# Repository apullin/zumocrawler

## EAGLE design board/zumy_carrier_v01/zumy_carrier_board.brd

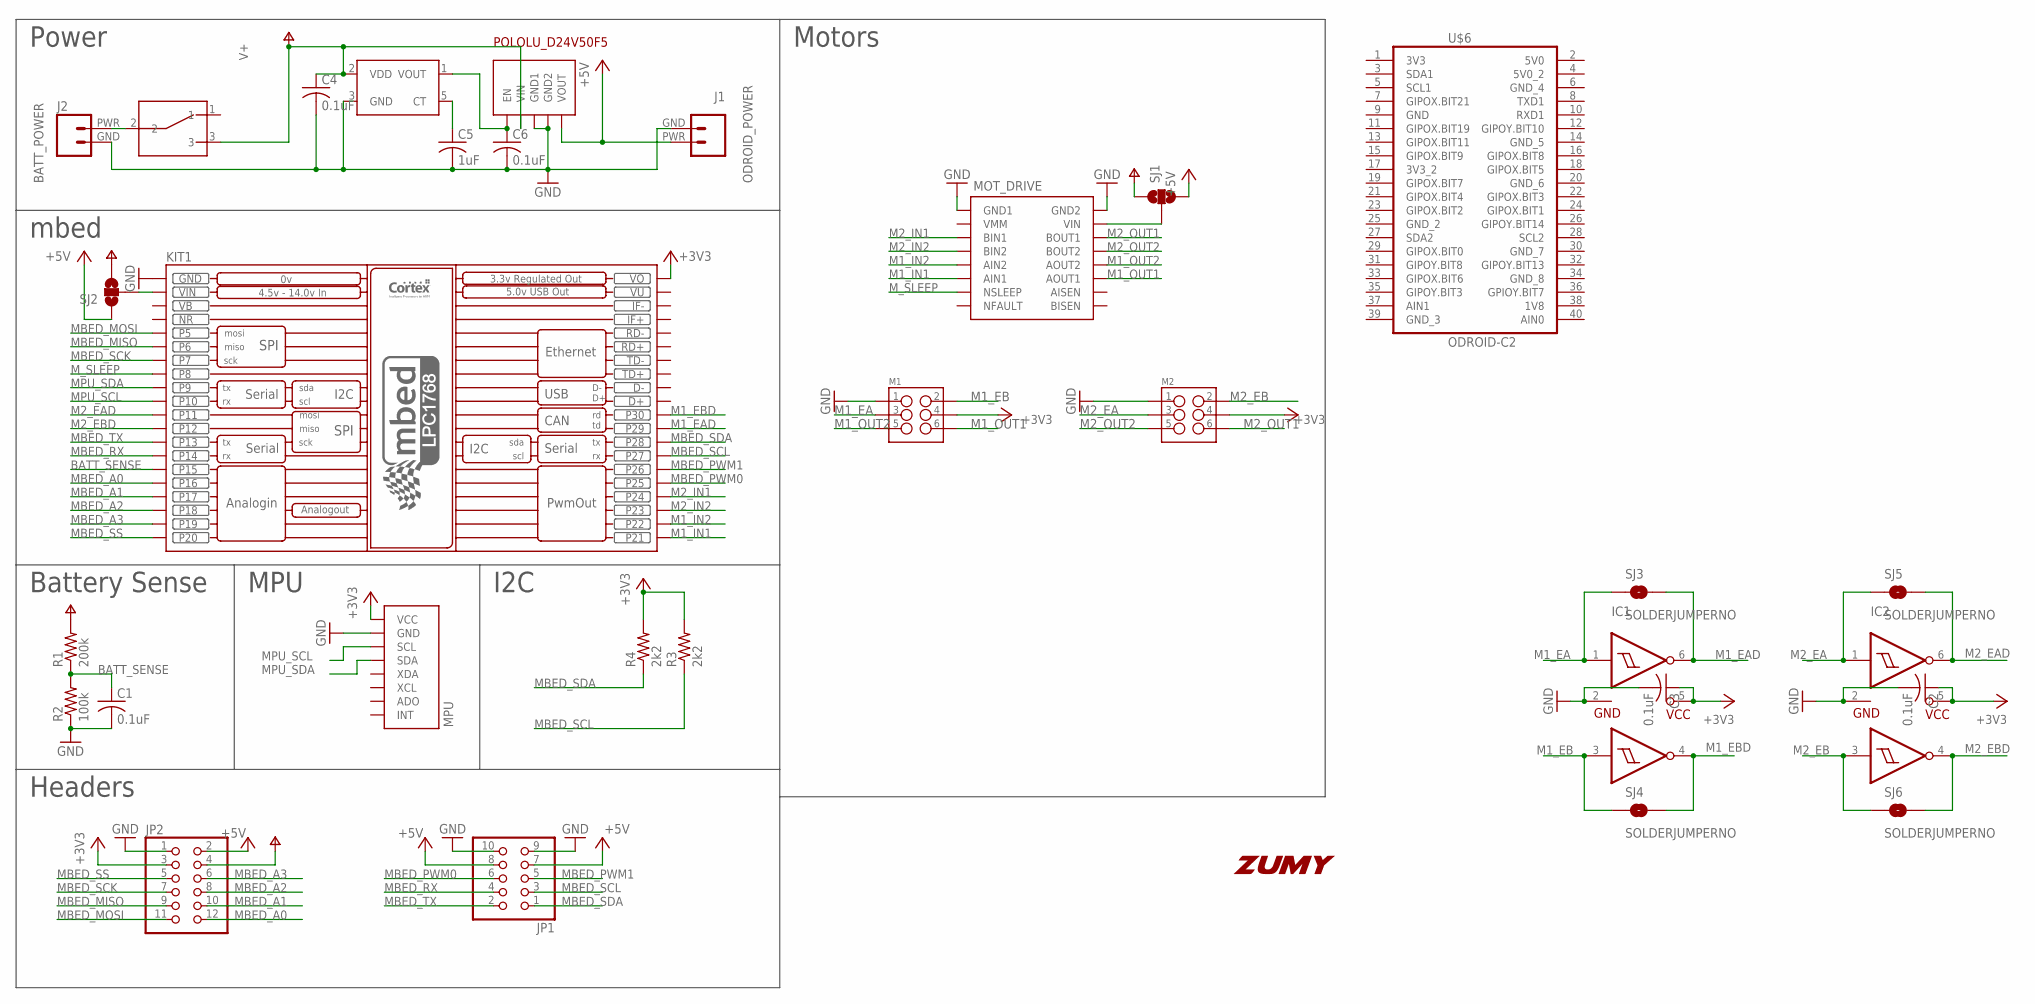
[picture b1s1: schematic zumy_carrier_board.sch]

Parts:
C1, C2, C3, C4, C6: 0.1uF; C1206
C5: 1uF; C1206
IC1, IC2: SN74AUP2G17; SC-70-6
J1: ODROID_POWER; ODOIRD_PWR
J2: BATT_POWER
JP1: PINHD-2X5; 2X05
JP2: PINHD-2X6; 2X06
KIT1: MBED_NXP_LPC1768; MBED-KIT
M1, M2: M03X2SHROUD; 2X3-SHROUDED
MOT_DRIVE: POLOLU_DRV8833_MODULE
MPU: ITG/MPU_MODULE
R1: 200k; R1206
R2: 100k; R1206
R3, R4: 2k2; R1206
SJ1, SJ2: SOLDERJUMPER_2WAYT; SJ_2
SJ3, SJ4, SJ5, SJ6: SOLDERJUMPERNO; SJ_2S-NO
SW1: 500SSP1S1M6QEA; 500SSP1S1M6QEA_SWITCH
U$2: BD5260G; SOT23-5
U$3: ZUMY_LOGO; ZUMY_LOGO_SILK
U$5: POLOLU_D24V50F5
U$6: ODROID-C2; ODROID-C2-BOARD

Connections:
+3V3: C2.1, C3.1, IC1.5 (VCC), IC2.5 (VCC), JP2.3, KIT1.VOUT (VO), M1.4, M2.4, MPU.VCC, R3.2, R4.2
+5V: J1.PWR, JP1.7, JP1.8, JP2.2, SJ1.3, SJ2.1, U$5.VOUT
BATT_SENSE: C1.1, KIT1.P$15 (P15), R1.1, R2.2
GND: C1.2, C2.2, C3.2, C4.2, C5.2, C6.2, IC1.2 (GND), IC2.2 (GND), J1.GND, J2.GND, JP1.9, JP1.10, JP2.1, KIT1.GND, M1.1, M2.1, MOT_DRIVE.GND1, MOT_DRIVE.GND2, MPU.GND, R2.1, U$2.3 (GND), U$5.GND1, U$5.GND2
M1_EA: IC1.1 (1A), M1.3, SJ3.1
M1_EAD: IC1.6 (1Y), KIT1.P$29 (P29), SJ3.2
M1_EB: IC1.3 (2A), M1.2, SJ4.1
M1_EBD: IC1.4 (2Y), KIT1.P$30 (P30), SJ4.2
M1_IN1: KIT1.P$21 (P21), MOT_DRIVE.AIN1
M1_IN2: KIT1.P$22 (P22), MOT_DRIVE.AIN2
M1_OUT1: M1.6, MOT_DRIVE.AOUT1
M1_OUT2: M1.5, MOT_DRIVE.AOUT2
M2_EA: IC2.1 (1A), M2.3, SJ5.1
M2_EAD: IC2.6 (1Y), KIT1.P$11 (P11), SJ5.2
M2_EB: IC2.3 (2A), M2.2, SJ6.1
M2_EBD: IC2.4 (2Y), KIT1.P$12 (P12), SJ6.2
M2_IN1: KIT1.P$24 (P24), MOT_DRIVE.BIN1
M2_IN2: KIT1.P$23 (P23), MOT_DRIVE.BIN2
M2_OUT1: M2.6, MOT_DRIVE.BOUT1
M2_OUT2: M2.5, MOT_DRIVE.BOUT2
MBED_A0: JP2.12, KIT1.P$16 (P16)
MBED_A1: JP2.10, KIT1.P$17 (P17)
MBED_A2: JP2.8, KIT1.P$18 (P18)
MBED_A3: JP2.6, KIT1.P$19 (P19)
MBED_MISO: JP2.9, KIT1.P$6 (P6)
MBED_MOSI: JP2.11, KIT1.P$5 (P5)
MBED_PWM0: JP1.6, KIT1.P$25 (P25)
MBED_PWM1: JP1.5, KIT1.P$26 (P26)
MBED_RX: JP1.4, KIT1.P$14 (P14)
MBED_SCK: JP2.7, KIT1.P$7 (P7)
MBED_SCL: JP1.3, KIT1.P$27 (P27), R3.1
MBED_SDA: JP1.1, KIT1.P$28 (P28), R4.1
MBED_SS: JP2.5, KIT1.P$20 (P20)
MBED_TX: JP1.2, KIT1.P$13 (P13)
MPU_SCL: KIT1.P$10 (P10), MPU.SCL
MPU_SDA: KIT1.P$9 (P9), MPU.SDA
M_SLEEP: KIT1.P$8 (P8), MOT_DRIVE.NSLEEP
unnamed: KIT1.VIN, SJ2.2
unnamed: J2.PWR, SW1.2
unnamed: MOT_DRIVE.VIN, SJ1.2
unnamed: C6.1, U$2.1 (VOUT), U$5.EN
unnamed: C5.1, U$2.5 (CT)
NR: KIT1.NR
V+: C4.1, JP2.4, R1.2, SJ1.1, SJ2.3, SW1.3, U$2.2 (VDD), U$5.VIN
VB: KIT1.VB
VU: KIT1.VU

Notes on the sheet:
Motors
Power
mbed
MPU
I2C
Headers
Battery Sense

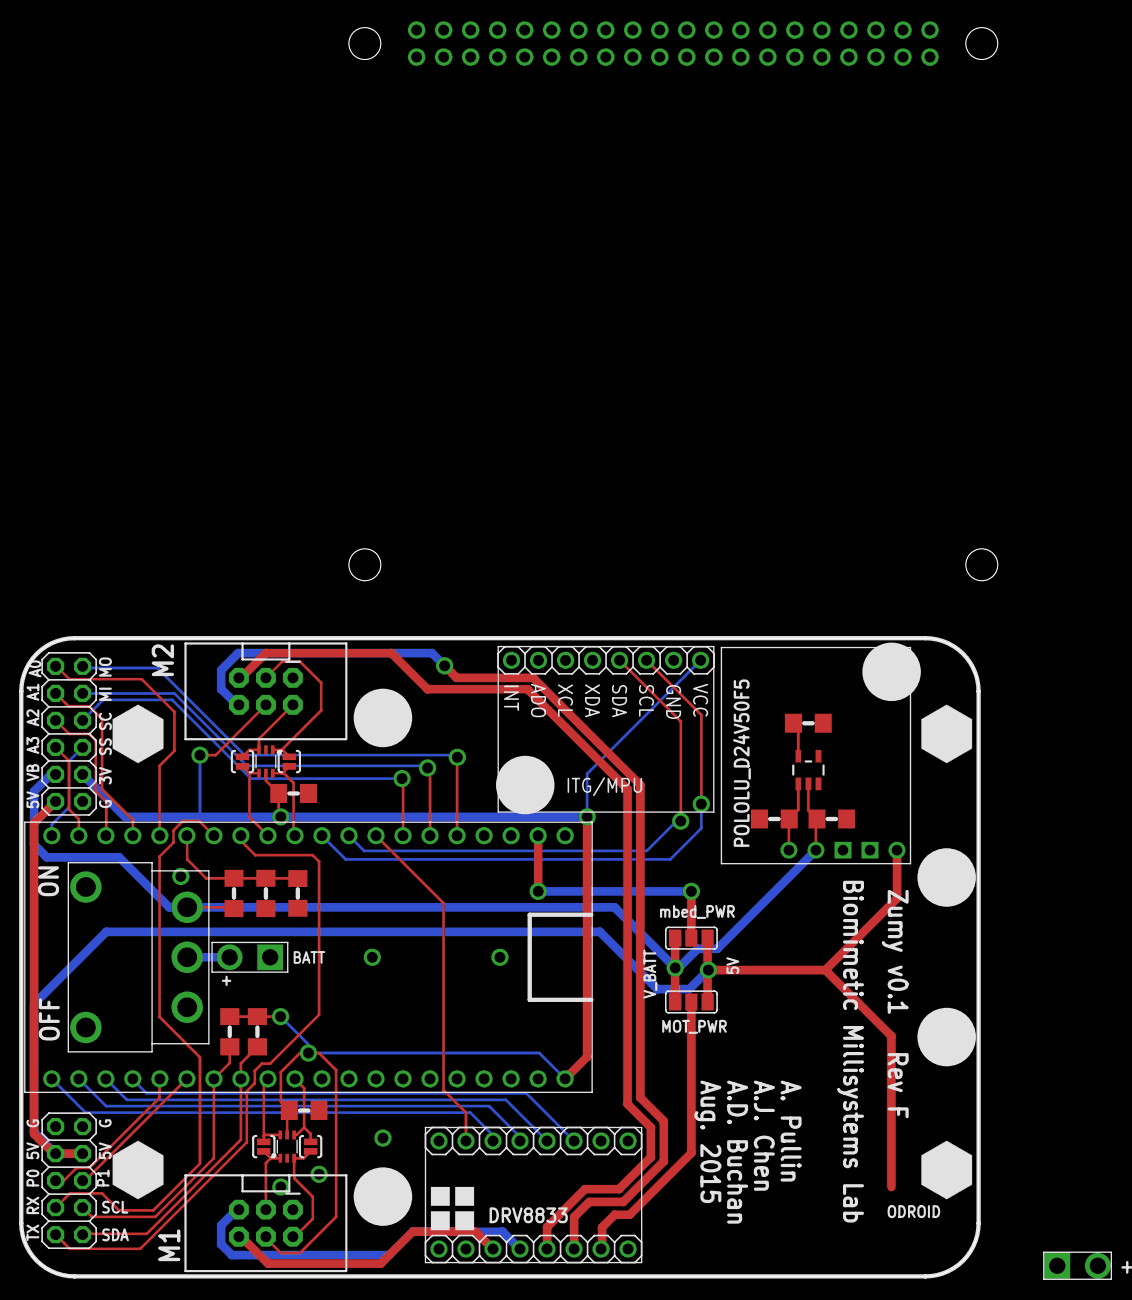
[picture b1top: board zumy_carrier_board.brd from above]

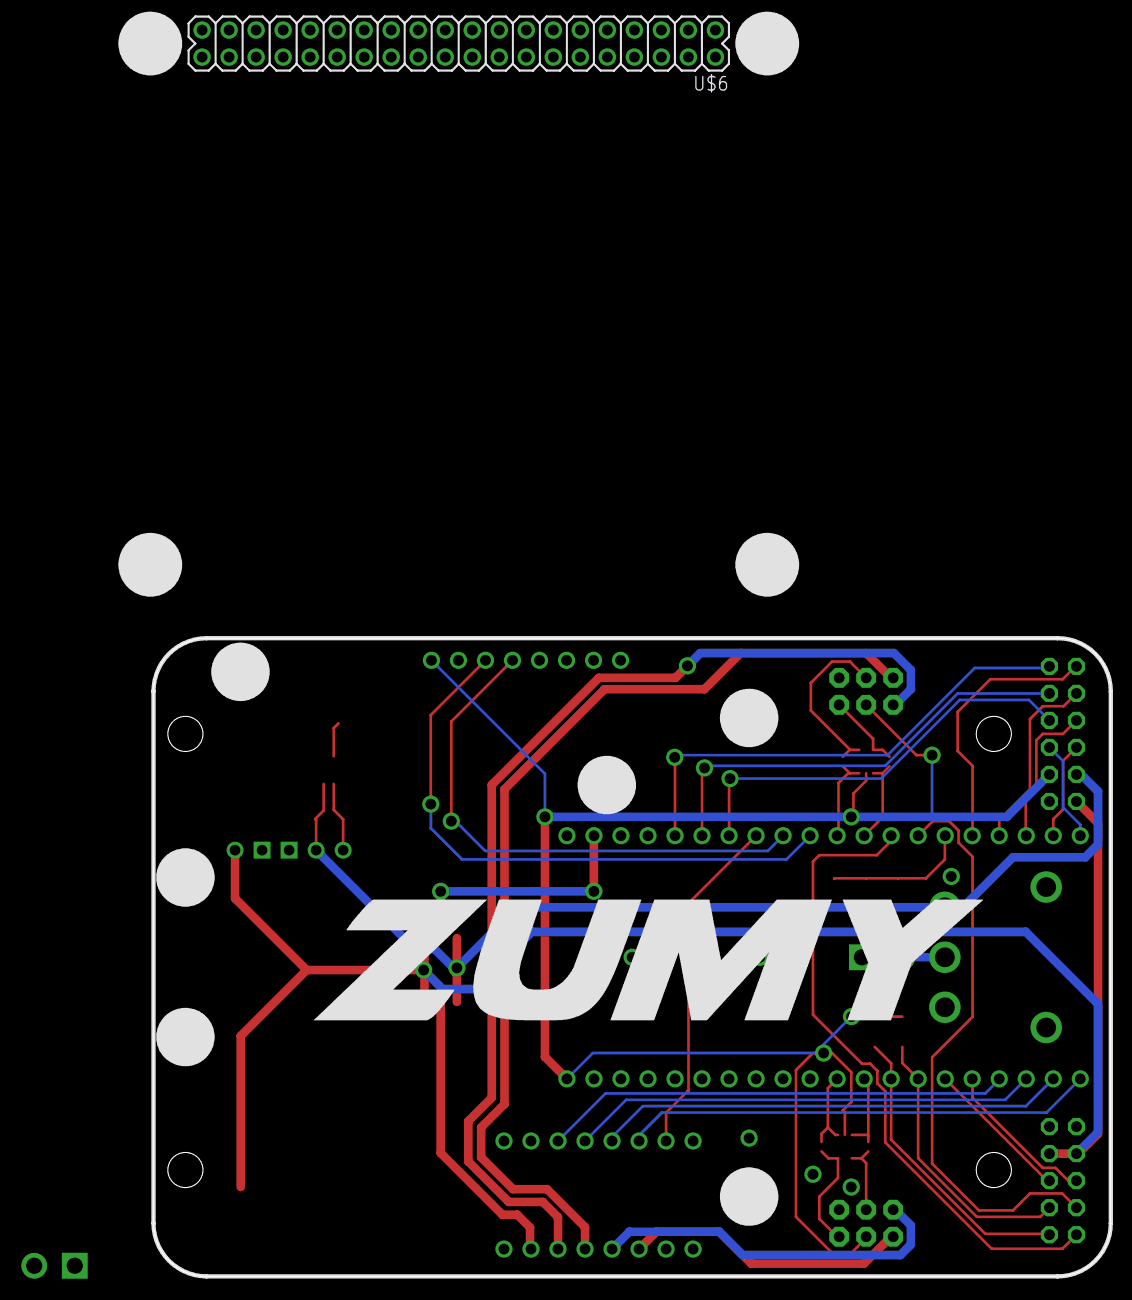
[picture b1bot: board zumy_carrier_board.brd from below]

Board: 2 copper layers, 90.0 x 60.0 mm, 34 parts (2 on the bottom side), 43 nets.

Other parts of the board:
U$1: CHASSIS_STANDOFF
U$4: ODROID_U3_MOUNTING

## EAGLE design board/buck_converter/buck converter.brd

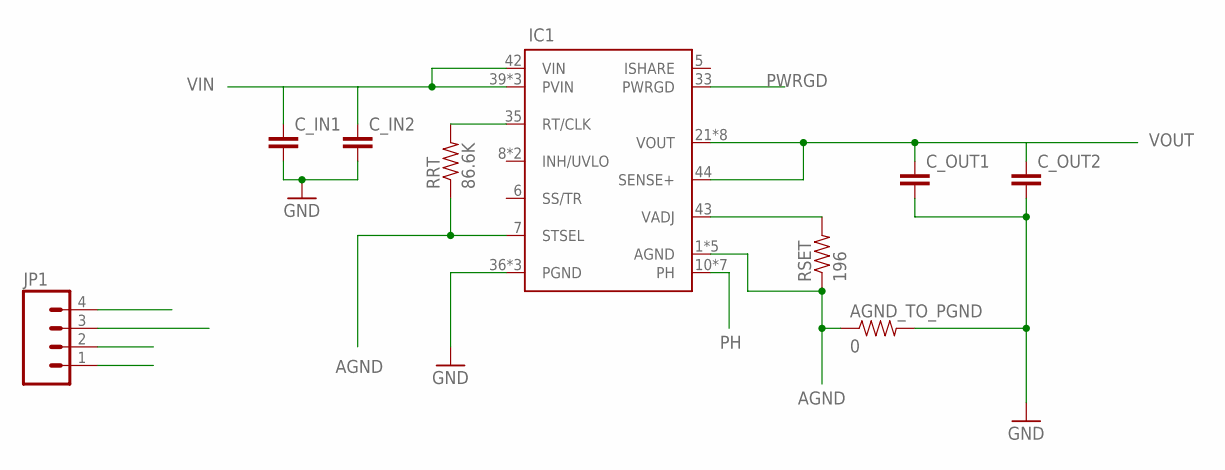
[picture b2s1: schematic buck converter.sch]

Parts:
AGND_TO_PGND: 0; 0402-RES
C_IN1, C_IN2: CAP1210; 1210
C_OUT1, C_OUT2: CAP1210; 1210
IC1: TPS84621
JP1: M04PTH; 1X04
RRT: 86.6K; 0402-RES
RSET: 196; 0402-RES

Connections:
AGND: AGND_TO_PGND.1, IC1.1 (AGND), IC1.2 (AGND), IC1.7 (STSEL), IC1.34 (AGND), IC1.45 (AGND), IC1.45B (AGND), RRT.1, RSET.1
GND: AGND_TO_PGND.2, C_IN1.2, C_IN2.2, C_OUT1.2, C_OUT2.2, IC1.36 (PGND), IC1.37 (PGND), IC1.38 (PGND), JP1.2
unnamed: IC1.35 (RT/CLK), RRT.2
unnamed: IC1.43 (VADJ), RSET.2
PH: IC1.10 (PH), IC1.11 (PH), IC1.12 (PH), IC1.13 (PH), IC1.14 (PH), IC1.17 (PH), IC1.46 (PH)
PWRGD: IC1.33 (PWRGD), JP1.4
VIN: C_IN1.1, C_IN2.1, IC1.39 (PVIN), IC1.40 (PVIN), IC1.41 (PVIN), IC1.42 (VIN), JP1.1
VOUT: C_OUT1.1, C_OUT2.1, IC1.21 (VOUT), IC1.24 (VOUT), IC1.25 (VOUT), IC1.26 (VOUT), IC1.27 (VOUT), IC1.28 (VOUT), IC1.29 (VOUT), IC1.44 (SENSE+), IC1.47 (VOUT), JP1.3

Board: 2 copper layers, 9 parts (0 on the bottom side), 8 nets, no tracks yet.

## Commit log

2014-06-24 Working on co2 publishing
2014-06-24 Looks like CO2 publishing is working
2014-08-27 Adding DESCRIPTION file to put title on LBR dir in Eagle.
2014-08-27 Start of Rev D board. Currently all ripped up.
2014-08-28 Most of Rev D done. Major rearrangement. New mounting hole pattern.
2014-08-29 Rev D done. Some library parts updated to suit new layout.
2014-08-30 Minor adjustments to placement.
2014-09-03 Added 6pin shrouded connectors for pololu encoder + motor drive. Routing is all screwed up.
2014-09-03 Adding in TI buck board module
2014-09-03 Added TPS84621 module to library.
2014-09-04 Adding gitignore for board file types.
2014-09-04 Initial schematic and board for custom buck converter based on TI chip.
2014-09-06 Some routing polygons added.
2014-09-09 Rev D now with encoder connectors, fully routed, no DRC errors.
2014-09-09 Update to project root .gitignore file to ignore Eagle temp file.
2014-09-09 Added dual schmitt trigger to library.
2014-09-09 Fix to schmitt trigger part in library.
2014-09-10 Rev D routed with schmitt triggers on encoders.
2014-09-15 Updates to labels, placements, layers, etc.
2014-09-15 Further minor changes to labels in tplace to enforce no line width < 0.006"
2014-09-15 Adeding customized CAM file for panelization script
2015-03-19 Useful script to start headless ipython notebook server on zumy.
2015-03-19 Update to Robot Test class to add LED switches. Needs to be ported to python dir code.
2015-06-13 Adding example image of board.
2015-08-10 Commiting last development since CO2 sensing
2015-08-10 Added Rev. E Parts (5V Reg with UVLO, Cap on vsense, caps on level translators). Before ripup and rearrange.
2015-08-11 Schematic and part placement mostly done. Need to clean up schematic, then fine adjust layout, then ready for routing.
2015-08-11 First pass at layout done
2015-08-11 Ready to Test on Othermill
2015-08-12 Pulled back switch from edge, just need to fix silkscreen.
2015-08-12 moved a few more traces. still need to do silkscreen.
2015-08-12 Silkscreen done, need to clean up for panelization
2015-08-12 Rename to use underscores.
2015-08-28 Adding voltage monitor breakout board.
2015-08-29 Finishing touches for Rev. F. Moved voltage regulator to not conflict with mbed USB cable. Added support post holes for accelerometer and voltage regulator. Increased drill for battery and odroid pow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
2016-03-04 Adding ODROID-C2 to library.
2016-03-15 Starting to shuffle board around for ODROID-C2 update.

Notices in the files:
parts and their libraries:
SparkFun-Connectors: Licensing: Creative Commons ShareAlike 4.0 International - https://creativecommons.org/licenses/by-sa/4.0
biomimetic: UC Regents. All rights reserved.
SparkFun-Passives: Licensing: CC v3.0 Share-Alike You are welcome to use this library for commercial purposes.
